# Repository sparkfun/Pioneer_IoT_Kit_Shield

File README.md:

Pioneer IoT Kit Shield
======================

[*Pioneer IoT Kit Shield (DEV-14531)*](https://www.sparkfun.com/products/14531)

The Pioneer IoT Add-On Shield is a unique board designed to add more functionality to the PSoC 6 from Cypress while remaining useful and practical for plenty of other Internet of Things applications. Each Add-On Shield is a pretty simple board with an equally simple layout that provides XBee, Qwiic and microSD functionality not only to the PSoC 6 but also to any board with an Arduino R3 shield format.

Repository Contents
-------------------

* **/Firmware** - Example projects for the PSoC 6 and PSoC 4BLE Pioneer kits.
* **/Hardware** - All Eagle design files (.brd, .sch)
* **/Production** - Test bed files and production panel files

Documentation
--------------
* **[Hookup Guide](https://learn.sparkfun.com/tutorials/using-the-psoc-6-pioneer-board-with-the-pioneer-iot-add-on-shield)** - Basic hookup guide for the Pioneer IoT Kit Shield.

License Information
-------------------

This product is _**open source**_! 

Please review the LICENSE.md file for license information. 

If you have any questions or concerns on licensing, please contact techsupport@sparkfun.com.

Distributed as-is; no warranty is given.

- Your friends at SparkFun.

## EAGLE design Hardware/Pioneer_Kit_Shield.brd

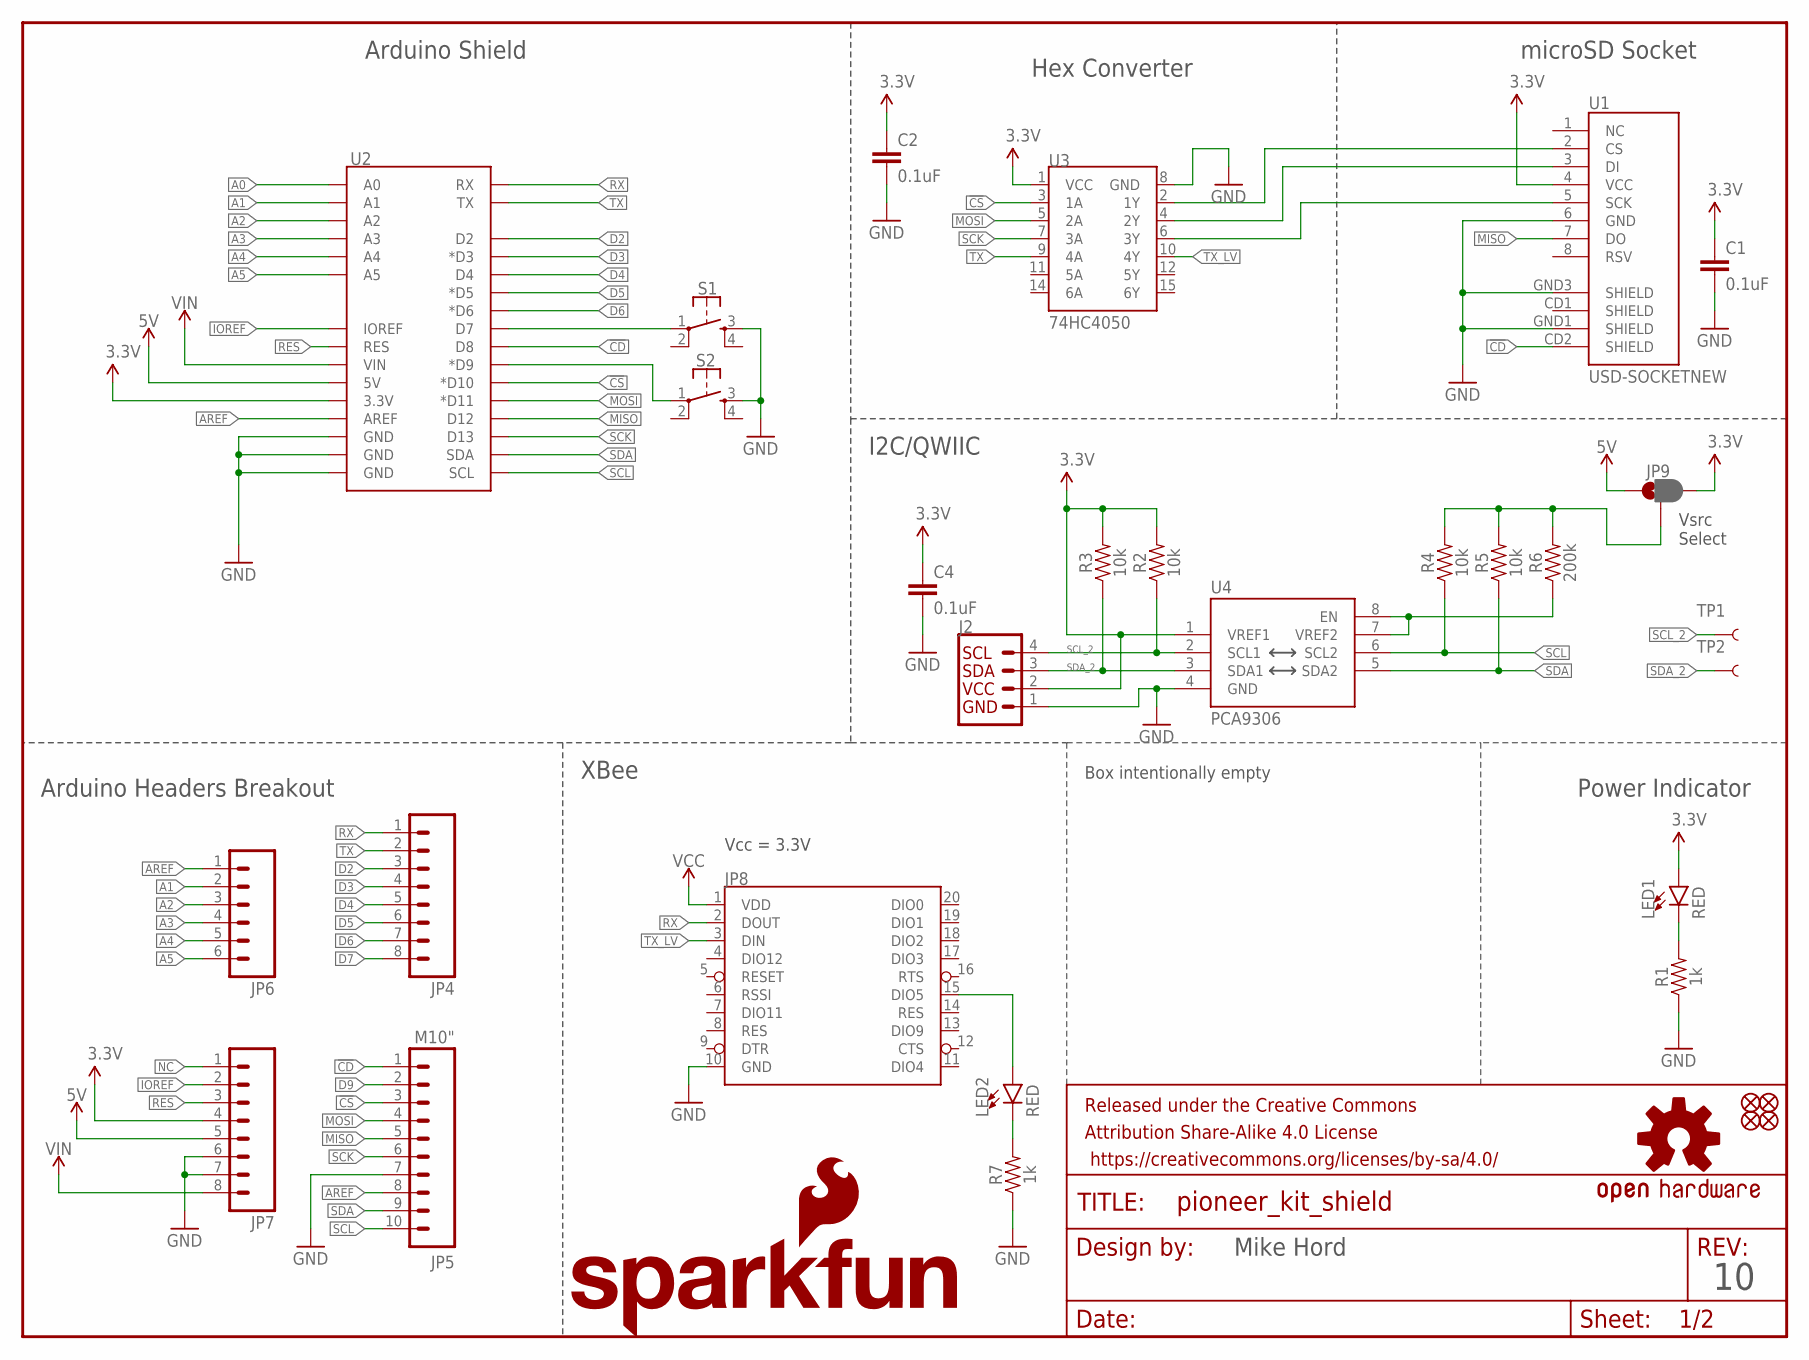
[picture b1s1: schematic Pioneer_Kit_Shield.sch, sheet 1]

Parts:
C1, C2, C4: 0.1uF; 0603
FRAME1: FRAME-LETTER; CREATIVE_COMMONS
J2: QWIIC_CONNECTORJS-1MM; 1X04_1MM_RA
JP1: SFE_LOGO_NAME_FLAME.1_INCH; SFE_LOGO_NAME_FLAME_.1
JP2, JP3, JP10, JP11: FIDUCIAL1X2; FIDUCIAL-1X2
JP4: M08; 1X08
JP5: M10"; 1X10
JP6: M06SIP; 1X06
JP7: M081X08; 1X08
JP8: XBEESMD; XBEE-SMD
JP9: JUMPER-SMT_3_1-NC_PASTE_SILK; SMT-JUMPER_3_1-NC_PASTE_SILK
LED1, LED2: RED; LED-0603
LOGO1: OSHW-LOGOM; OSHW-LOGO-M
R1, R7: 1k; 0603
R2, R3, R4, R5: 10k; 0603
R6: 200k; 0603
S1, S2: MOMENTARY-SWITCH-SPST-2-SMD-5.2MM; TACTILE_SWITCH_SMD_5.2MM
TP1, TP2: TEST-POINTTP_15TH_THRU; TP_15TH
U1: USD-SOCKETNEW; MICRO-SD-SOCKET-PP
U2: ARDUINO_UNO_R3_SHIELDUNO_R3_SHIELD_NOLABELS_LOCK; UNO_R3_SHIELD_NOLABELS_LOCK
U3: 74HC4050; SO16
U4: PCA9306; PCA9306DC

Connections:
3.3V: C1.1, C2.1, C4.1, J2.2 (VCC), JP7.4, JP9.3, LED1.A, R2.2, R3.2, U1.4 (VCC), U2.3.3V, U3.1 (VCC), U4.1 (VREF1)
5V: JP7.5, JP9.1, U2.5V; also elsewhere on the board
!CD: JP5.1, U1.CD2 (SHIELD), U2.D8
!CS: JP5.3, U2.D10 (*D10), U3.3 (1A)
A0: JP6.1, U2.A0
A1: JP6.2, U2.A1
A2: JP6.3, U2.A2
A3: JP6.4, U2.A3
A4: JP6.5, U2.A4
A5: JP6.6, U2.A5
AREF: JP5.8, U2.AREF
D2: JP4.3, U2.D2
D3: JP4.4, U2.D3 (*D3)
D4: JP4.5, U2.D4
D5: JP4.6, U2.D5 (*D5)
D6: JP4.7, U2.D6 (*D6)
D7: JP4.8, S1.1, U2.D7
D9: JP5.2, S2.1, U2.D9 (*D9)
GND: C1.2, C2.2, C4.2, J2.1 (GND), JP5.7, JP7.6, JP7.7, JP8.10 (GND), R1.1, R7.1, S1.3, S2.3, U1.6 (GND), U1.GND1 (SHIELD), U1.GND3 (SHIELD), U2.GND@0 (GND), U2.GND@1 (GND), U2.GND@2 (GND), U3.8 (GND), U4.4 (GND); also elsewhere on the board
IOREF: JP7.2, U2.IOREF
MISO: JP5.5, U1.7 (DO), U2.D12
MOSI: JP5.4, U2.D11 (*D11), U3.5 (2A)
unnamed: LED2.C, R7.2
unnamed: U1.3 (DI), U3.4 (2Y)
unnamed: JP8.15 (DIO5), LED2.A
unnamed: U1.5 (SCK), U3.6 (3Y)
unnamed: LED1.C, R1.2
unnamed: JP9.2, R4.2, R5.2, R6.2
unnamed: R6.1, U4.7 (VREF2), U4.8 (EN)
unnamed: U1.2 (CS), U3.2 (1Y)
NC: JP7.1
RES: JP7.3, U2.RES
RX: JP4.1, JP8.2 (DOUT), U2.RX
SCK: JP5.6, U2.D13, U3.7 (3A)
SCL: JP5.10, R4.1, U2.SCL, U4.6 (SCL2)
SCL_2: J2.4 (SCL), R2.1, TP1.P$1, U4.2 (SCL1)
SDA: JP5.9, R5.1, U2.SDA, U4.5 (SDA2)
SDA_2: J2.3 (SDA), R3.1, TP2.P$1, U4.3 (SDA1)
TX: JP4.2, U2.TX, U3.9 (4A)
TX_LV: JP8.3 (DIN), U3.10 (4Y)
VCC: JP8.1 (VDD); also elsewhere on the board
VIN: JP7.8, U2.VIN

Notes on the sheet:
Power Indicator
Arduino Headers Breakout
microSD Socket
Hex Converter
Arduino Shield
Mike Hord
I2C/QWIIC
XBee
Box intentionally empty
Vcc = 3.3V
Vsrc Select

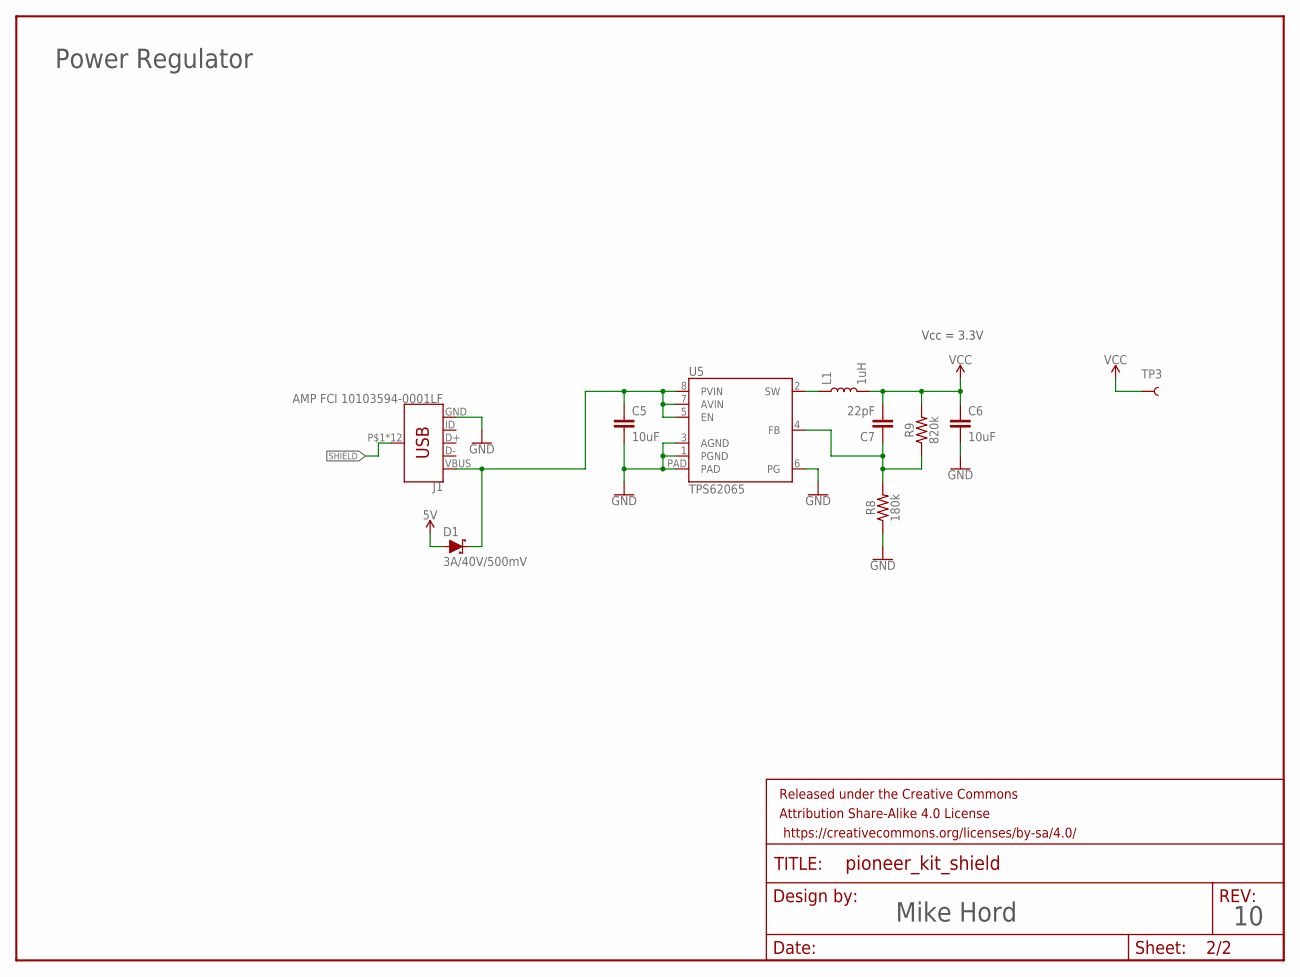
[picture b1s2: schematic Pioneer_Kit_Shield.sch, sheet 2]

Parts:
C5: 10uF; 0805
C6: 10uF; 0603
C7: 22pF; 0603
D1: 3A/40V/500mV; SMA-DIODE
FRAME2: FRAME-LETTERNO_PACKAGE; DUMMY
J1: AMP FCI 10103594-0001LF; USB-MICROB-PTH
L1: 1uH; INDUCTOR-SRP4020
R8: 180k; 0603
R9: 820k; 0603
TP3: TEST-POINTTP_15TH_THRU; TP_15TH
U5: TPS62065; WSON-8-PAD

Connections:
5V: D1.A; also elsewhere on the board
GND: C5.2, C6.2, J1.GND, R8.1, U5.1 (PGND), U5.3 (AGND), U5.6 (PG), U5.PAD; also elsewhere on the board
unnamed: C5.1, D1.C, J1.VBUS, U5.5 (EN), U5.7 (AVIN), U5.8 (PVIN)
unnamed: C7.1, R8.2, R9.1, U5.4 (FB)
unnamed: L1.P$1 (1), U5.2 (SW)
SHIELD: J1.P$1 (SHIELD), J1.P$2 (SHIELD), J1.P$3 (SHIELD), J1.P$4 (SHIELD), J1.P$6 (SHIELD), J1.P$8 (SHIELD), J1.P$10 (SHIELD), J1.P$12 (SHIELD), J1.SHEILD2 (SHIELD), J1.SHIELD, J1.SHIELD3 (SHIELD), J1.SHIELD4 (SHIELD)
VCC: C6.1, C7.2, L1.P$2 (2), R9.2, TP3.P$1; also elsewhere on the board

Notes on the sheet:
Mike Hord
Vcc = 3.3V
Power Regulator

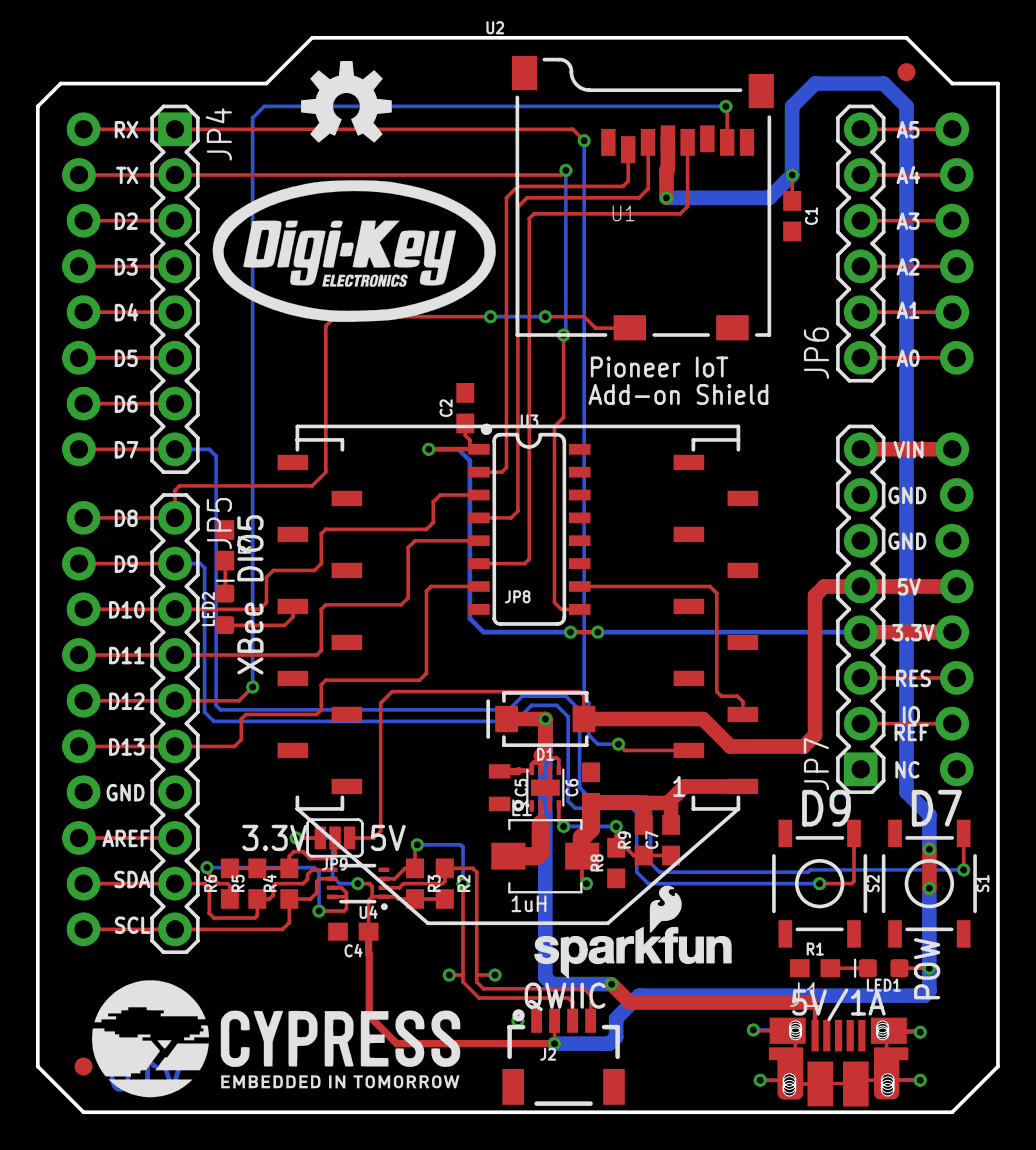
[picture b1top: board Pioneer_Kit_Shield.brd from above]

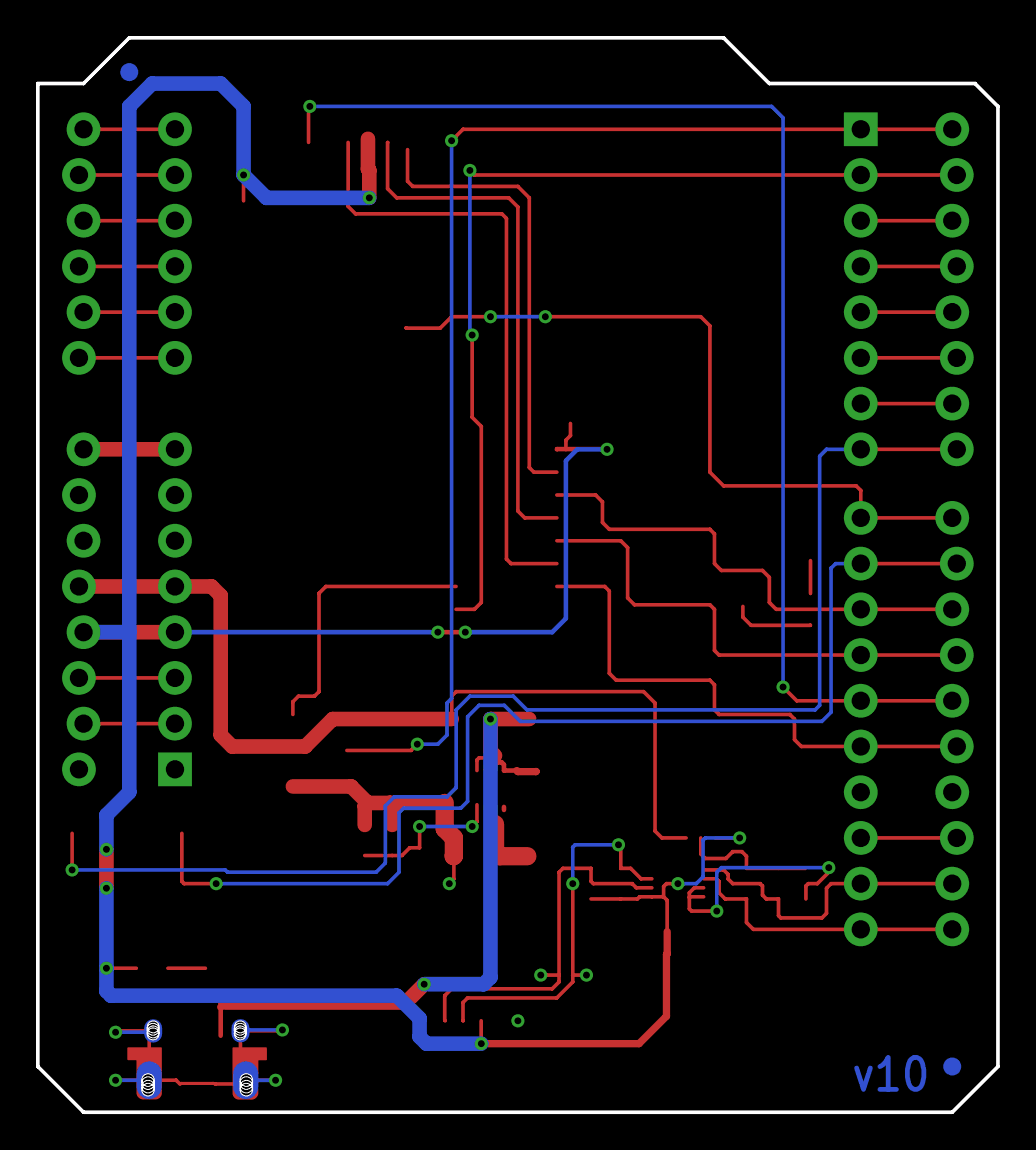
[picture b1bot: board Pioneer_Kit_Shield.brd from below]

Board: 2 copper layers, 53.3 x 59.7 mm, 45 parts (2 on the bottom side), 45 nets.

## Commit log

2017-10-24 Initial post-copy commit
2017-11-09 Final version before review
2017-11-15 Changes from review
2017-11-16 Fixed issues from QC double check
2017-11-27 Initial commit of Env Sensor firmware
2017-11-28 Added testpoints
2017-11-30 Prior to converting to Bosch API
2017-12-08 Interim checkpoint - - XBee Wifi Example works - Environmental Sensor Example works - Changed Digi-Key logo on PCB
2017-12-08 Added Env Sensor, XBee Wifi Example
2017-12-12 Couple of changes to v10
2017-12-19 Getting all examples in or out as they should be
2018-01-05 Added IoT_Hub Example Project
2018-01-08 Update to beta 2 version of projects
2018-01-08 Fixed pathing issue on IoT_HUb project
2018-02-01 Fixed README.md
2018-02-07 Added BLE central example
2018-02-07 Remove deprecated Environmental_Sensor firmware
2018-02-08 Uncommented XBee init function in PSoC6 example
2018-02-16 Modified code for more reliable CCS811 functionality
2018-05-03 Remove specific info re wifi and thingspeak api

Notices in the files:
parts and their libraries:
SparkFun-Aesthetics: Licensing: CC v3.0 Share-Alike You are welcome to use this library for commercial purposes.
SparkFun-Aesthetics: Released under the Creative Commons Attribution Share-Alike 4.0 License
SparkFun-Aesthetics: https://creativecommons.org/licenses/by-sa/4.0
